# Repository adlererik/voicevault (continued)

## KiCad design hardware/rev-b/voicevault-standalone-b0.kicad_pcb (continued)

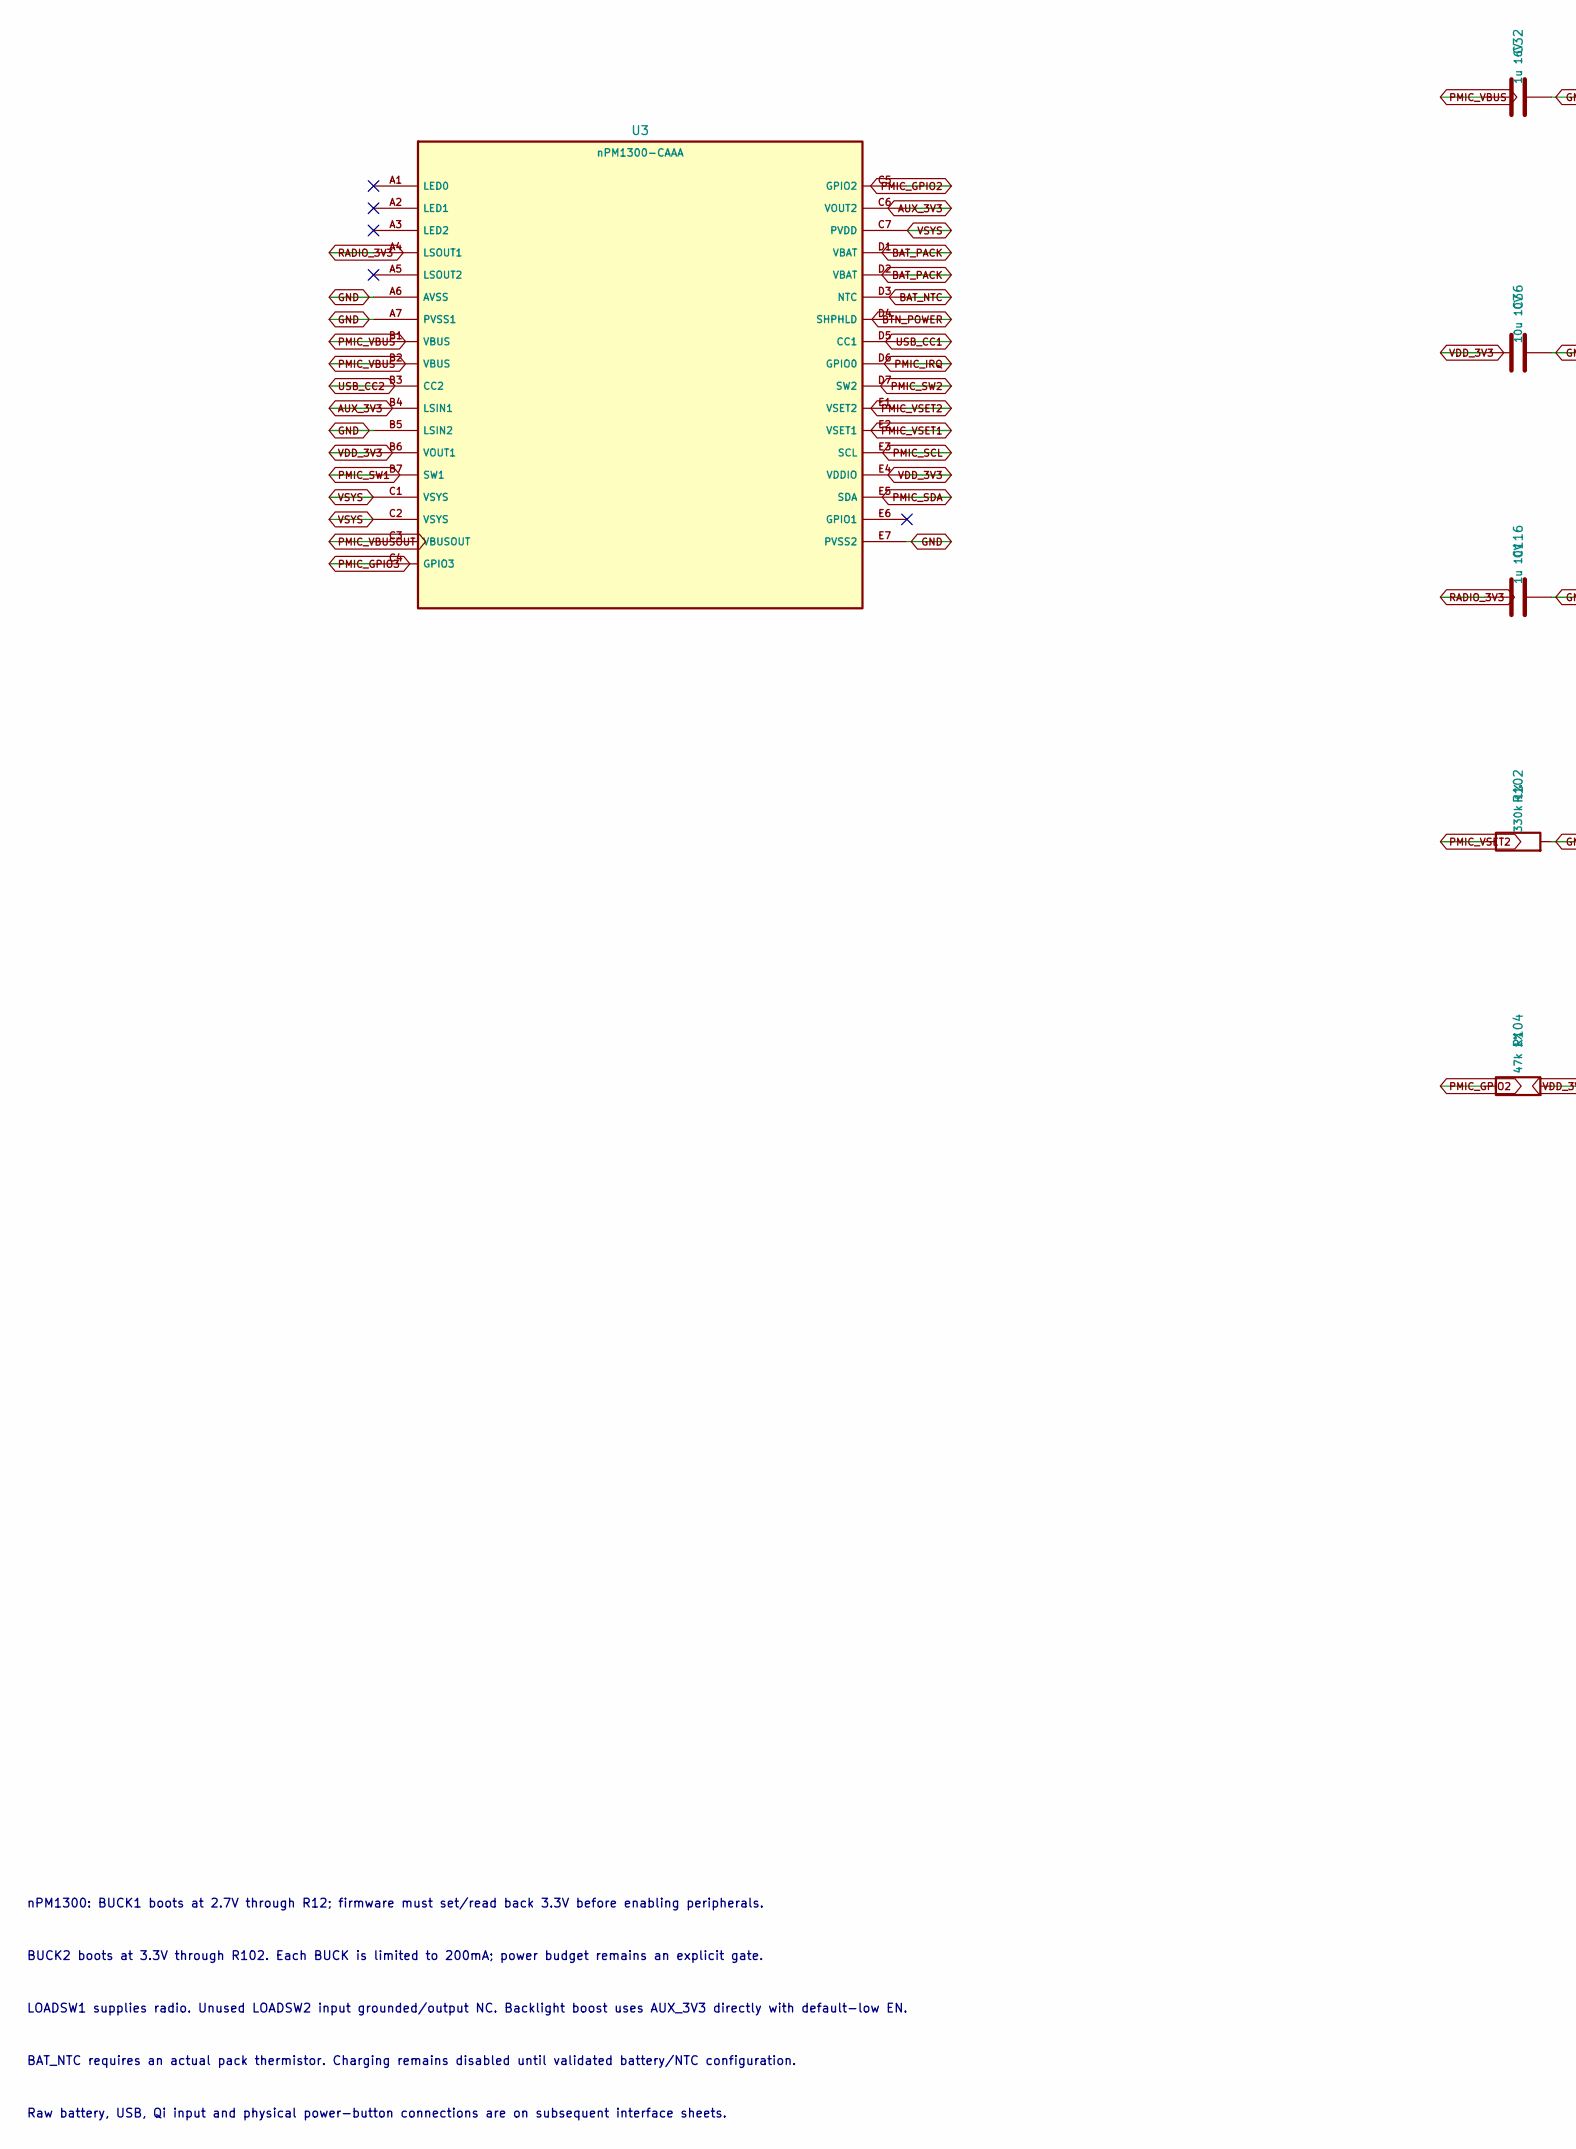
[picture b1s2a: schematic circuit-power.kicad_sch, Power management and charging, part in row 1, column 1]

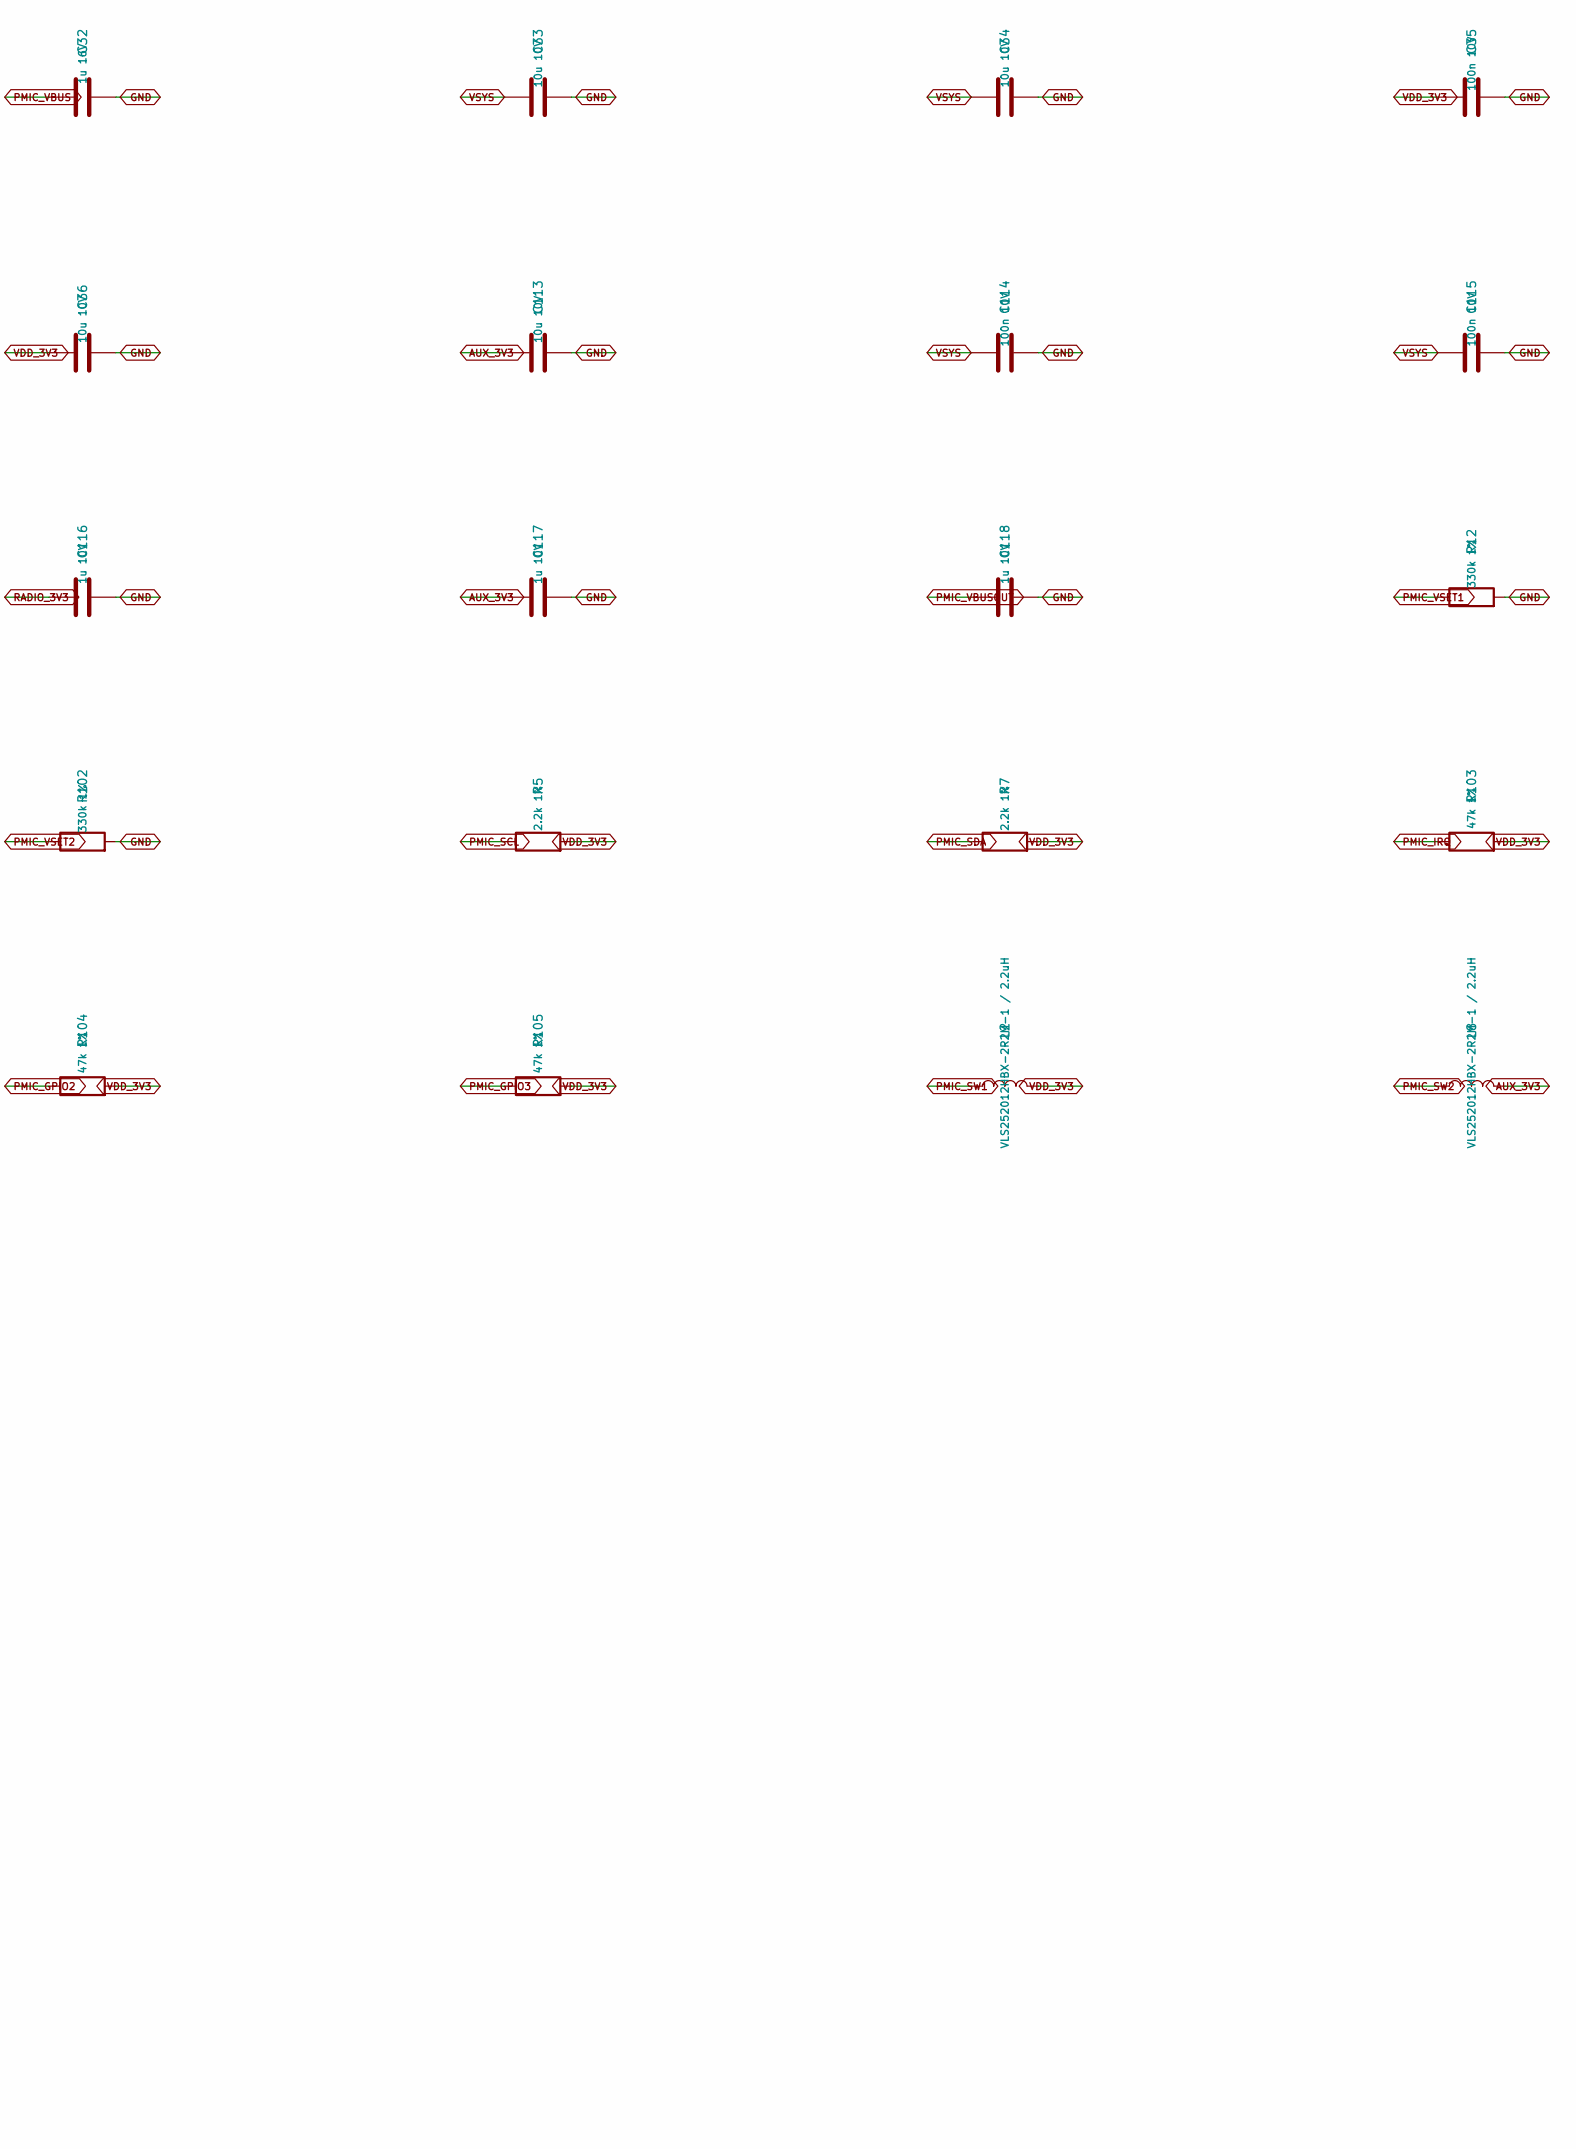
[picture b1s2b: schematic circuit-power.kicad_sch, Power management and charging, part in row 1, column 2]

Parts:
C32: 1u 16V; C_0603_1608Metric
C33, C34, C36, C113: 10u 10V; C_0603_1608Metric
C35, C114, C115: 100n 10V; C_0603_1608Metric
C116, C117, C118: 1u 10V; C_0603_1608Metric
L2, L8: VLS252012HBX-2R2M-1 / 2.2uH; L_1008_2520Metric
R5, R7: 2.2k 1%; R_0402_1005Metric
R12, R102: 330k 1%; R_0402_1005Metric
R103, R104, R105: 47k 1%; R_0402_1005Metric
U3: nPM1300-CAAA; nPM1300_CAAA_Nordic

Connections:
AUX_3V3: C113.1, C117.1, L8.2, U3.B4 (LSIN1), U3.C6 (VOUT2); also elsewhere on the board
BAT_NTC: U3.D3 (NTC); also elsewhere on the board
BAT_PACK: U3.D1 (VBAT), U3.D2 (VBAT); also elsewhere on the board
BTN_POWER: U3.D4 (SHPHLD); also elsewhere on the board
GND: C32.2, C33.2, C34.2, C35.2, C36.2, C113.2, C114.2, C115.2, C116.2, C117.2, C118.2, R12.2, R102.2, U3.A6 (AVSS), U3.A7 (PVSS1), U3.B5 (LSIN2), U3.E7 (PVSS2); also elsewhere on the board
PMIC_GPIO2: R104.1, U3.C5 (GPIO2); also elsewhere on the board
PMIC_GPIO3: R105.1, U3.C4 (GPIO3); also elsewhere on the board
PMIC_IRQ: R103.1, U3.D6 (GPIO0); also elsewhere on the board
PMIC_SCL: R5.1, U3.E3 (SCL); also elsewhere on the board
PMIC_SDA: R7.1, U3.E5 (SDA); also elsewhere on the board
PMIC_SW1: L2.1, U3.B7 (SW1)
PMIC_SW2: L8.1, U3.D7 (SW2)
PMIC_VBUS: C32.1, U3.B1 (VBUS), U3.B2 (VBUS); also elsewhere on the board
PMIC_VBUSOUT: C118.1, U3.C3 (VBUSOUT)
PMIC_VSET1: R12.1, U3.E2 (VSET1)
PMIC_VSET2: R102.1, U3.E1 (VSET2)
RADIO_3V3: C116.1, U3.A4 (LSOUT1); also elsewhere on the board
USB_CC1: U3.D5 (CC1); also elsewhere on the board
USB_CC2: U3.B3 (CC2); also elsewhere on the board
VDD_3V3: C35.1, C36.1, L2.2, R5.2, R7.2, R103.2, R104.2, R105.2, U3.B6 (VOUT1), U3.E4 (VDDIO); also elsewhere on the board
VSYS: C33.1, C34.1, C114.1, C115.1, U3.C1 (VSYS), U3.C2 (VSYS), U3.C7 (PVDD); also elsewhere on the board

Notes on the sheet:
nPM1300: BUCK1 boots at 2.7V through R12; firmware must set/read back 3.3V before enabling peripherals.
BUCK2 boots at 3.3V through R102. Each BUCK is limited to 200mA; power budget remains an explicit gate.
LOADSW1 supplies radio. Unused LOADSW2 input grounded/output NC. Backlight boost uses AUX_3V3 directly with default-low EN.
BAT_NTC requires an actual pack thermistor. Charging remains disabled until validated battery/NTC configuration.
Raw battery, USB, Qi input and physical power-button connections are on subsequent interface sheets.

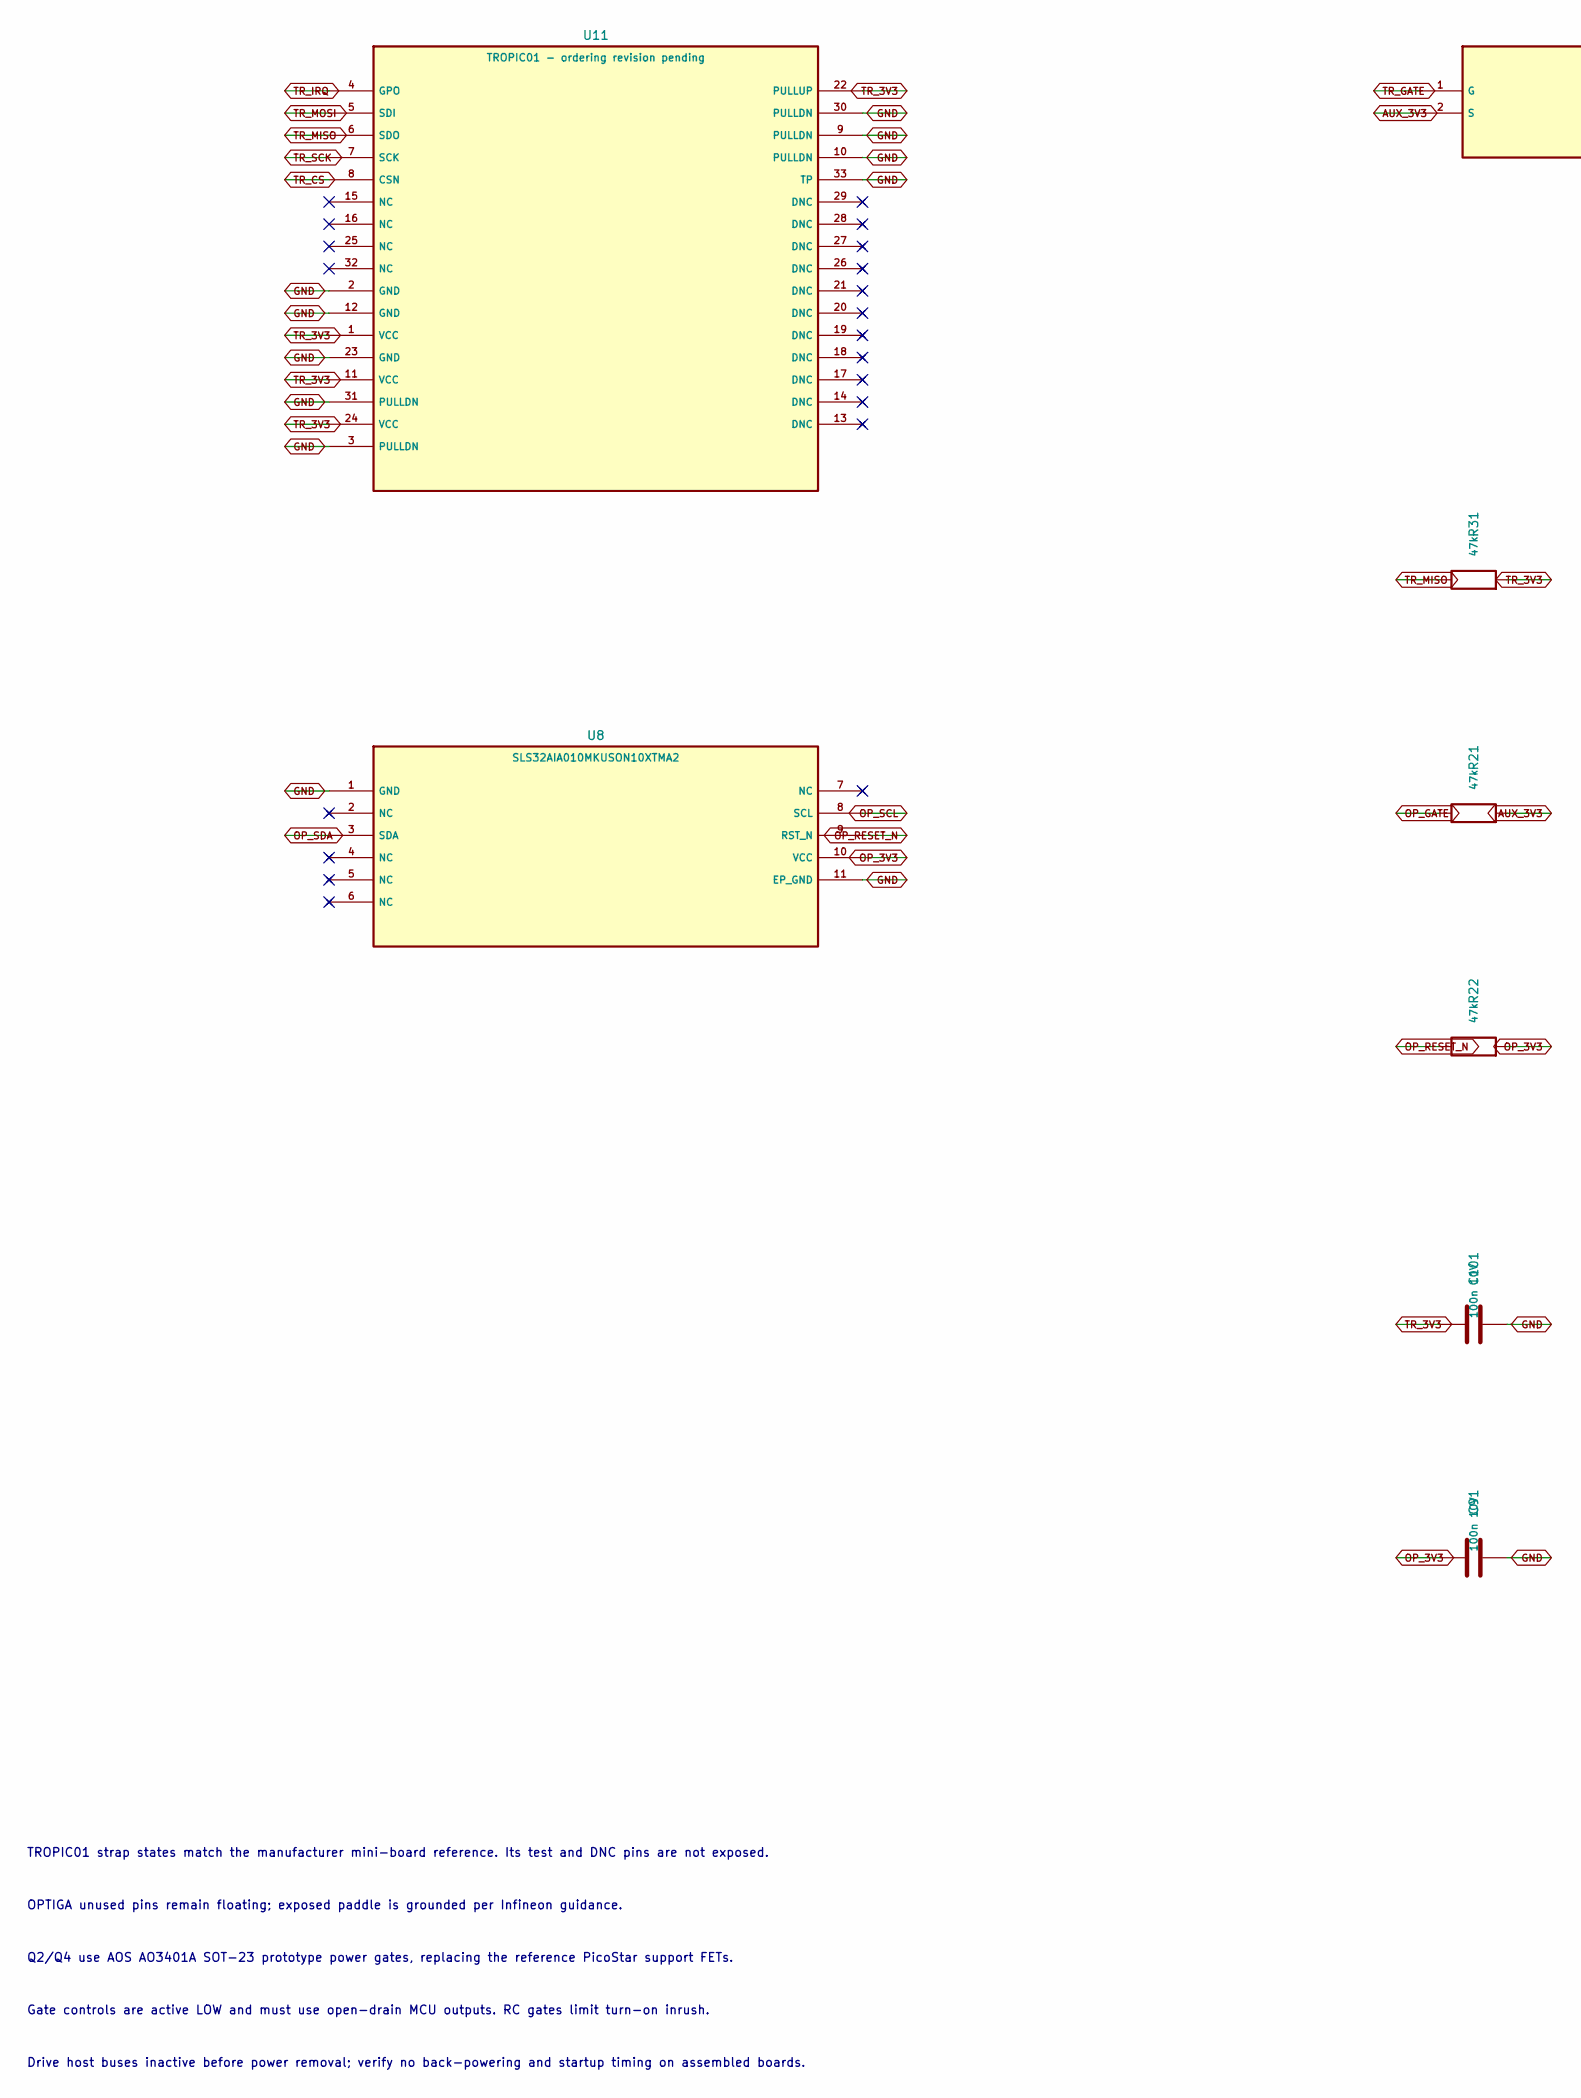
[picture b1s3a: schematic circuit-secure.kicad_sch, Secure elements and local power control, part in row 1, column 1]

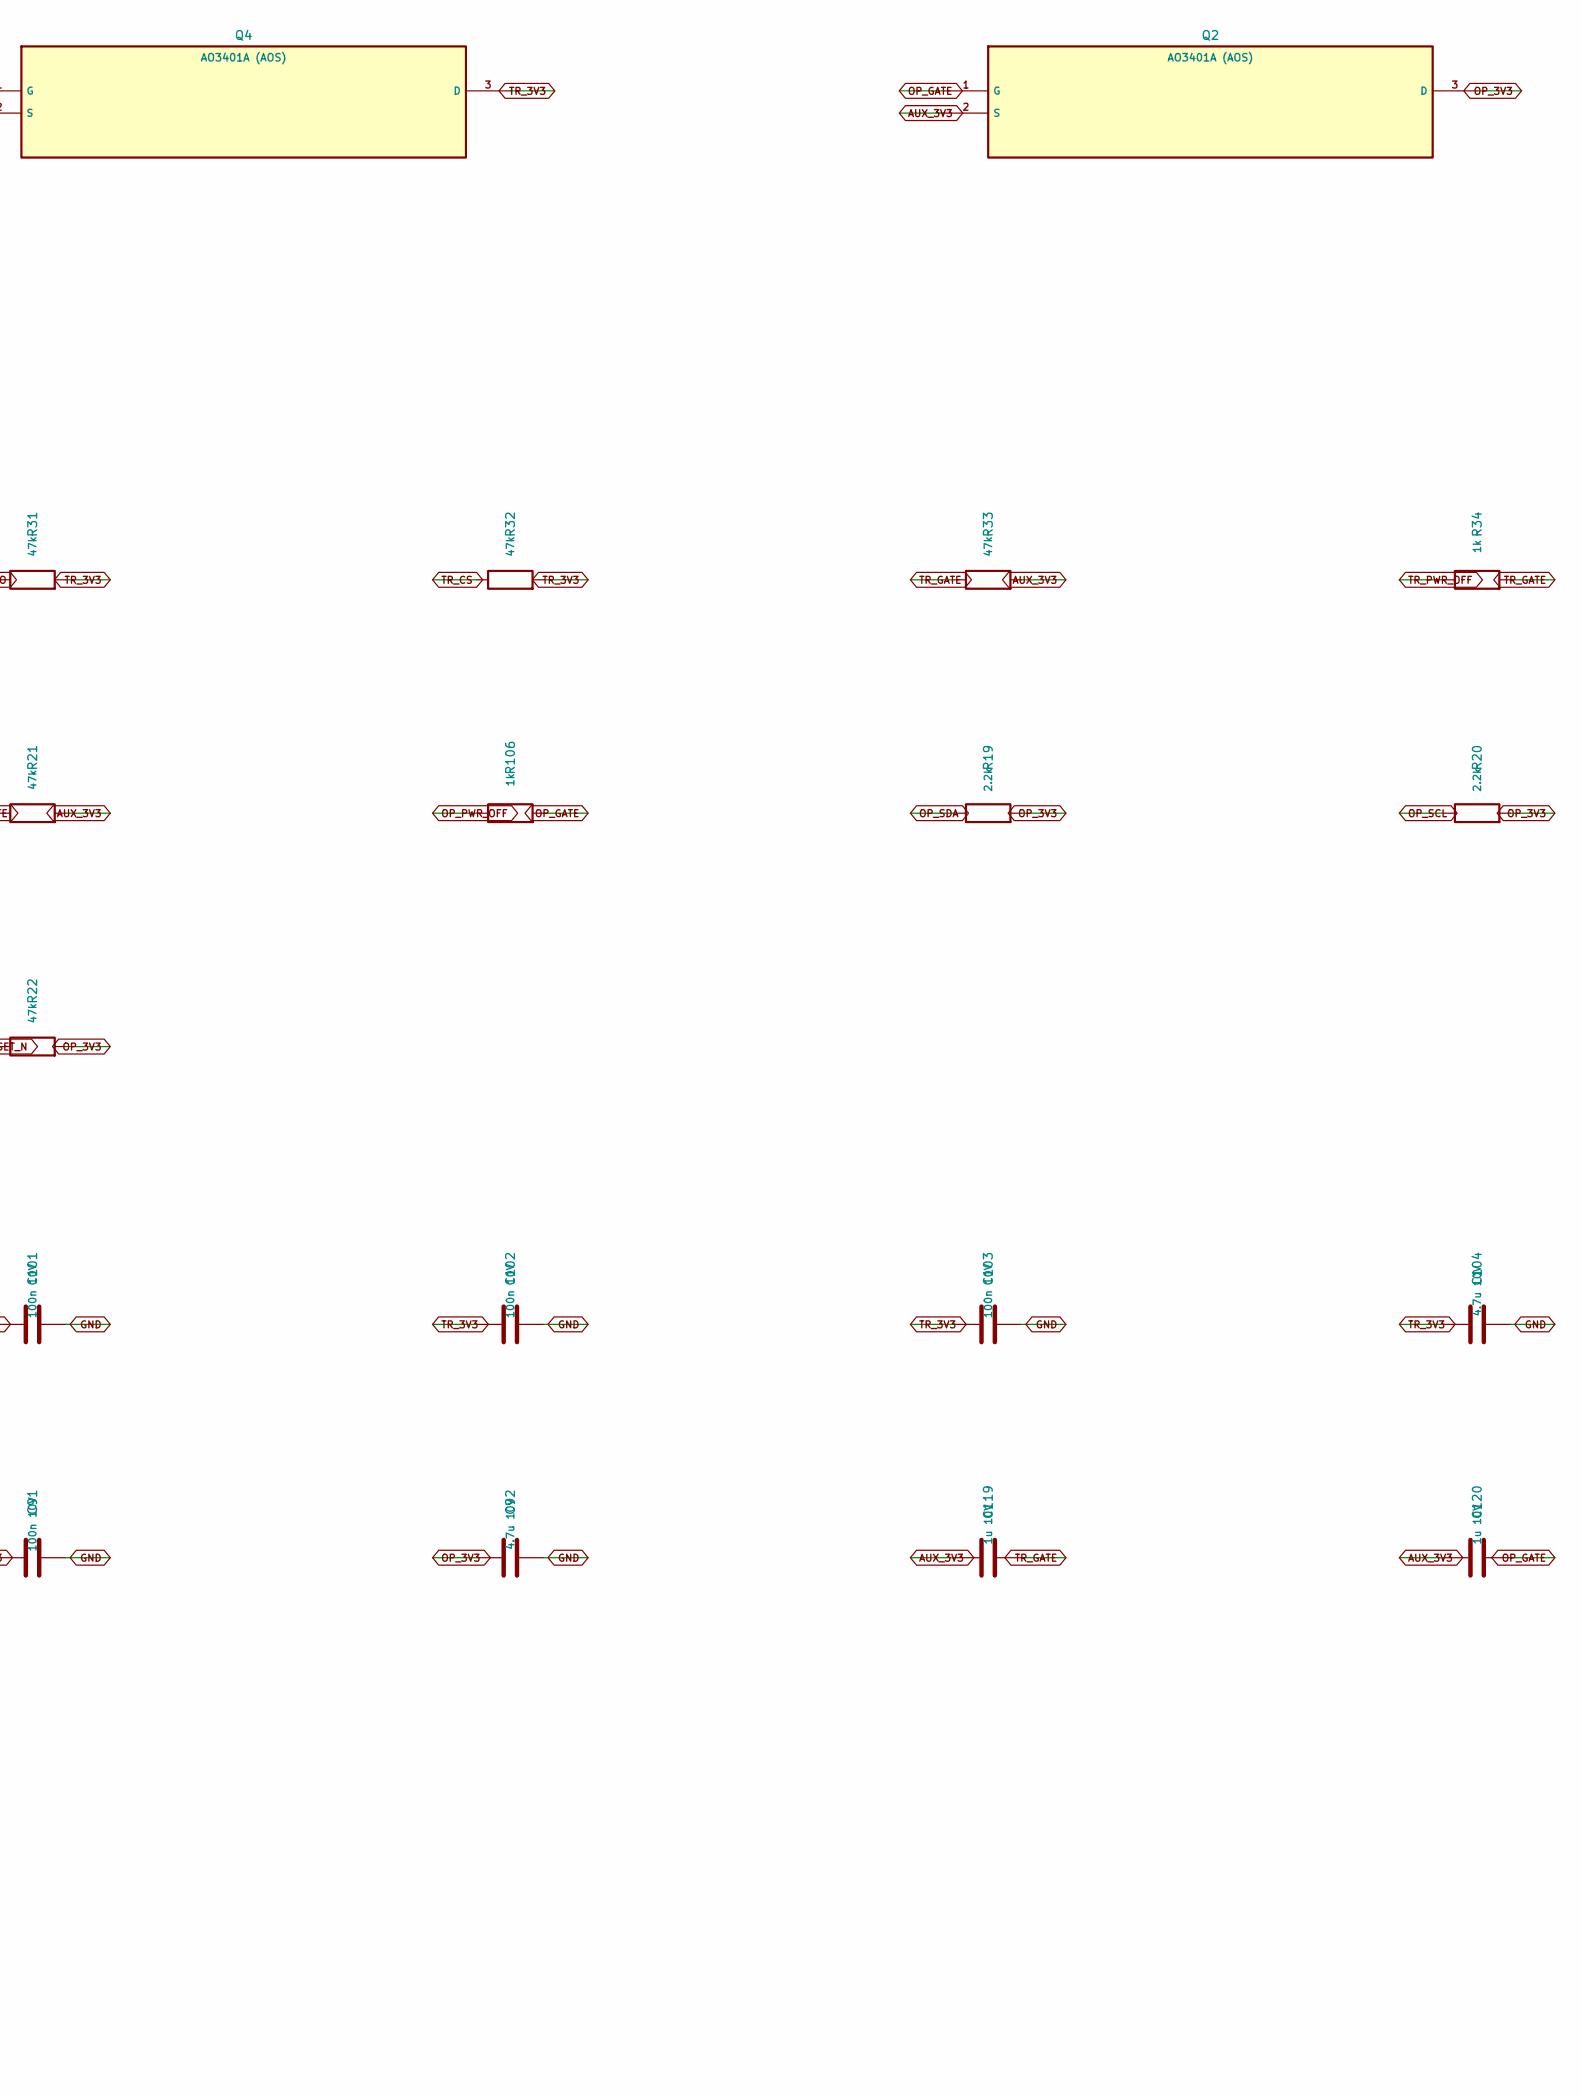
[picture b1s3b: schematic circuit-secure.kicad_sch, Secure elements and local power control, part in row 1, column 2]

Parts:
C91, C101, C102, C103: 100n 10V; C_0402_1005Metric
C92, C104: 4.7u 10V; C_0603_1608Metric
C119, C120: 1u 10V; C_0402_1005Metric
Q2, Q4: AO3401A (AOS); SOT-23
R19, R20: 2.2k; R_0402_1005Metric
R21, R22, R31, R32, R33: 47k; R_0402_1005Metric
R34, R106: 1k; R_0402_1005Metric
U8: SLS32AIA010MKUSON10XTMA2; OPTIGA_PG_USON10_2
U11: TROPIC01 - ordering revision pending; TROPIC01_QFN32_vendor

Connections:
AUX_3V3: C119.1, C120.1, Q2.2 (S), Q4.2 (S), R21.2, R33.2; also elsewhere on the board
GND: C91.2, C92.2, C101.2, C102.2, C103.2, C104.2, U8.1 (GND), U8.11 (EP_GND), U11.2 (GND), U11.3 (PULLDN), U11.9 (PULLDN), U11.10 (PULLDN), U11.12 (GND), U11.23 (GND), U11.30 (PULLDN), U11.31 (PULLDN), U11.33 (TP); also elsewhere on the board
OP_3V3: C91.1, C92.1, Q2.3 (D), R19.2, R20.2, R22.2, U8.10 (VCC); also elsewhere on the board
OP_GATE: C120.2, Q2.1 (G), R21.1, R106.2
OP_PWR_OFF: R106.1; also elsewhere on the board
OP_RESET_N: R22.1, U8.9 (RST_N); also elsewhere on the board
OP_SCL: R20.1, U8.8 (SCL); also elsewhere on the board
OP_SDA: R19.1, U8.3 (SDA); also elsewhere on the board
TR_3V3: C101.1, C102.1, C103.1, C104.1, Q4.3 (D), R31.2, R32.2, U11.1 (VCC), U11.11 (VCC), U11.22 (PULLUP), U11.24 (VCC); also elsewhere on the board
TR_CS: R32.1, U11.8 (CSN); also elsewhere on the board
TR_GATE: C119.2, Q4.1 (G), R33.1, R34.2
TR_IRQ: U11.4 (GPO); also elsewhere on the board
TR_MISO: R31.1, U11.6 (SDO); also elsewhere on the board
TR_MOSI: U11.5 (SDI); also elsewhere on the board
TR_PWR_OFF: R34.1; also elsewhere on the board
TR_SCK: U11.7 (SCK); also elsewhere on the board

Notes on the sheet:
TROPIC01 strap states match the manufacturer mini-board reference. Its test and DNC pins are not exposed.
OPTIGA unused pins remain floating; exposed paddle is grounded per Infineon guidance.
Q2/Q4 use AOS AO3401A SOT-23 prototype power gates, replacing the reference PicoStar support FETs.
Gate controls are active LOW and must use open-drain MCU outputs. RC gates limit turn-on inrush.
Drive host buses inactive before power removal; verify no back-powering and startup timing on assembled boards.

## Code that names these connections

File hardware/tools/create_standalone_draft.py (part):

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    debug = {'3': 'VDD_3V3', '4': 'MCU_SWDIO', '5': 'GND', '6': 'MCU_SWCLK',
             '7': 'GND', '8': 'MCU_SWO', '11': 'GND', '12': 'MCU_NRST',
             '13': 'MCU_UART_RX', '14': 'MCU_UART_TX'}
    mcu_signals = {'PA13': 'MCU_SWDIO', 'PA14': 'MCU_SWCLK', 'PB3': 'MCU_SWO',
                   'NRST': 'MCU_NRST', 'PC8': 'MCU_UART_RX', 'PC9': 'MCU_UART_TX'}
    circuits_file = DEST / 'circuits.json'
    if circuits_file.exists():
        mcu_signals.update(json.loads(circuits_file.read_text()).get('mcu_signals', {}))
    absent = set(mcu_signals) - {pin['name'] for pin in pins}
    if absent:
        raise RuntimeError('Signals assigned to pins absent from the selected UFBGA144 part: ' + ', '.join(sorted(absent)))
    expected = {'PA13': 'C10', 'PA14': 'B11', 'PB3': 'D6', 'NRST': 'J2',
                'PC8': 'D12', 'PC9': 'F8'}
    for pin_name, ball in expected.items():
        assert next(pin for pin in pins if pin['name'] == pin_name)['number'] == ball
    root_id = uid('schematic')
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        (25, 23, 'NOT FOR FABRICATION. Hierarchical circuits under review; all PCB routing remains incomplete.'),
        (190, 125, 'STDC14 pin 3 is target voltage sense, NOT a power input.'),
        (190, 133, 'Use an external STLINK-V3MINIE. Target supply is separate.'),
        (190, 141, 'Pins 13/14 use TARGET RX/TX naming. UART6 on PC8/PC9.'),
        (190, 158, 'Power, radio, secure elements, controls and offline-update interfaces: see child sheets.'),
        (190, 166, 'Main debug and radio debug are separate; probes measure target voltage only.'),
        (190, 174, 'Display/touch, haptic, Qi and NFC are on separate reviewed-source circuit sheets.'),
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
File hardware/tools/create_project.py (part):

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    parts.append(item)

parts += [
    dict(ref='R1', name='2.2k mic bias', pins={'1':'MICBIAS','2':'CODEC_MIC'}, at=[140,113], sch=[240,160], footprint='Resistor_SMD:R_0603_1608Metric'),
    dict(ref='R2', name='10k mute sense', pins={'1':'3V3','2':'MIC_SENSE'}, at=[105,112], sch=[240,175], footprint='Resistor_SMD:R_0603_1608Metric'),
    dict(ref='R3', name='47k SD deselect', pins={'1':'3V3','2':'SD_CS'}, at=[110,100], sch=[170,190], footprint='Resistor_SMD:R_0603_1608Metric'),
    dict(ref='R4', name='10k SE deselect', pins={'1':'3V3','2':'SE_CS'}, at=[60,103], sch=[170,205], footprint='Resistor_SMD:R_0603_1608Metric'),
    dict(ref='C1', name='100n 16V', pins={'1':'3V3','2':'GND'}, at=[65,110], sch=[40,210], footprint='Capacitor_SMD:C_0603_1608Metric'),
    dict(ref='C2', name='10u 16V', pins={'1':'3V3','2':'GND'}, at=[70,110], sch=[100,210], footprint='Capacitor_SMD:C_0805_2012Metric'),
    dict(ref='C3', name='22u 16V', pins={'1':'5V_SYS','2':'GND'}, at=[85,110], sch=[40,225], footprint='Capacitor_SMD:C_1210_3225Metric'),
    dict(ref='C4', name='220u 10V HP left', pins={'1':'HP_L_RAW','2':'HP_L'}, at=[163,112], sch=[320,110], footprint='Capacitor_THT:CP_Radial_D6.3mm_P2.50mm'),
    dict(ref='C5', name='220u 10V HP right', pins={'1':'HP_R_RAW','2':'HP_R'}, at=[163,124], sch=[320,125], footprint='Capacitor_THT:CP_Radial_D6.3mm_P2.50mm'),
    dict(ref='SW1', name='Physical mic disconnect', pins={'1':'HEADSET_MIC','2':'CODEC_MIC','3':'GND','4':'GND','5':'MIC_SENSE','6':None}, at=[125,110], sch=[250,205], footprint='Button_Switch_THT:SW_CK_JS202011CQN_DPDT_Straight'),
]

symbols = []
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
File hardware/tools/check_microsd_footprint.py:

#!/usr/bin/env python3
"""Compare the selected socket's actual native lands with reviewed drawing data.

SD-104031-001 rev B2 sheet 1: KiCad's local origin/view is rotated 180 degrees
relative to the recommended PCB layout. Latest delivered revision and assembly
acceptance are separate gates; the drawing-copy provenance is recorded in Git.
"""
import json
from pathlib import Path
import pcbnew

ROOT=Path(__file__).resolve().parents[2]
DESIGN=ROOT/'hardware/rev-b'

def main():
    footprint=pcbnew.FootprintLoad(str(DESIGN/'VoiceVault_B0.pretty'),'microSD_HC_Molex_104031-0811')
    assert footprint is not None
    expected={str(i+1):[(x,-5.45,.85,1.1)] for i,x in enumerate([-3.105,-2.005,-.905,.195,1.295,2.395,3.495])}
    expected.update({'8':[(4.545,-5.45,.75,1.1)],'9':[(-5.74,.7,1.2,1)],'10':[(-5.74,4.4,1.2,1)],
        'SH':[(-5.565,-5.325,1.55,1.35),(-2.24,5.375,1.9,1.35),(3.73,5.375,1.9,1.35),(5.755,-5.1,1.17,1.8)]})
    actual={}
    for p in footprint.Pads():
        actual.setdefault(p.GetNumber(),[]).append((p.GetPosition().x,p.GetPosition().y,p.GetSize().x,p.GetSize().y))
    integer=lambda values:sorted(tuple(pcbnew.FromMM(v) for v in row) for row in values)
    assert set(actual)==set(expected)
    for number in expected:
        # Library serialization is exact to 1nm; allow 2nm conversion rounding.
        assert all(abs(a-b)<=2 for aa,bb in zip(sorted(actual[number]),integer(expected[number])) for a,b in zip(aa,bb)),number
        assert len(actual[number])==len(expected[number]),number
    board=pcbnew.LoadBoard(str(DESIGN/'voicevault-standalone-b0.kicad_pcb'))
    socket=next(f for f in board.GetFootprints() if f.GetReference()=='J401')
    assert socket.GetValue()=='1040310811' and socket.GetFPID().GetLibItemName()=='microSD_HC_Molex_104031-0811'
    mapping={'1':'SD_DAT2','2':'SD_CS_N','3':'SD_MOSI','4':'SD_3V3','5':'SD_SCK','6':'GND','7':'SD_MISO','8':'SD_DAT1','9':'SD_DETECT_N','10':'GND','SH':'GND'}
    assert {p.GetNumber():p.GetNetname() for p in socket.Pads()}==mapping
    assert len(list(socket.Pads()))==14
    assert socket.GetLayer()==pcbnew.F_Cu
    scratch=pcbnew.BOARD();scratch.Add(footprint)
    footprint.SetOrientationDegrees(socket.GetOrientationDegrees());footprint.SetPosition(socket.GetPosition())
    world=lambda f:sorted((p.GetNumber(),p.GetPosition().x,p.GetPosition().y,p.GetSize().x,p.GetSize().y,p.GetOrientationDegrees()%360) for p in f.Pads())
    for a,z in zip(world(footprint),world(socket)):
        assert a[0]==z[0] and all(abs(x-y)<=2 for x,y in zip(a[1:5],z[1:5])) and abs(a[5]-z[5])<1e-6,'Actual board land differs from reviewed pattern'
    out=ROOT/'.lab-runs/hardware/standalone-b0/microsd-footprint.json'
    result=dict(result='pass',part='Molex 1040310811',drawing='SD-104031-001 rev B2 sheet 1',
        logical_pins=11,physical_pads=14,actual_board_pin_nets_verified=True,actual_board_land_geometry_verified=True,
        normally_open_card_detect_closes_to_ground=True,
        scope='Nominal reviewed land geometry and pin mapping; not latest-revision, sourcing or physical qualification')
    out.parent.mkdir(parents=True,exist_ok=True);out.write_text(json.dumps(result,indent=2)+'\n')
    print(json.dumps(result,indent=2))

if __name__=='__main__':main()
